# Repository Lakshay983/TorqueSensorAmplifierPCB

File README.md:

# TorqueSensorAmplifierPCB
PCB that amplifies an input signal from a torque sensor to be fed into an ADC

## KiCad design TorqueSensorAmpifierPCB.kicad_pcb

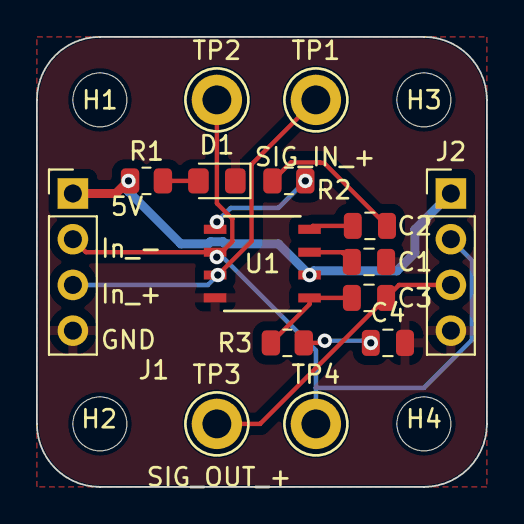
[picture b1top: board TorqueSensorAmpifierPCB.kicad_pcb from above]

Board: 2 copper layers, 25.0 x 25.0 mm, 19 parts (0 on the bottom side), 12 nets.

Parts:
C1: 1uF; C_0805_2012Metric
C2: 10uF; C_0805_2012Metric
C3: 250uF; C_0805_2012Metric
C4: .05uF; C_0805_2012Metric
D1: Green; LED_0805_2012Metric_Pad1.15x1.40mm_HandSolder
H1, H2, H3, H4: MountingHole; MountingHole_3mm
J1, J2: Conn_01x04_Socket; PinHeader_1x04_P2.54mm_Vertical
R1: 5k; R_0805_2012Metric
R2: 1.2k; R_0805_2012Metric
R3: 10; R_0805_2012Metric
TP1, TP2, TP3, TP4: TestPoint; TestPoint_Keystone_5005-5009_Compact
U1: LM386; M08A_TEX-L

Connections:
+5V: J1.1, J2.1, R1.1, U1.6 (V+)
/SIG_IN_+: J1.3, TP1.1, U1.3 (+)
/SIG_OUT_+: C3.2, J2.3, TP3.1
GND: C1.2, C4.2, D1.1 (K), J1.4, J2.4, U1.4 (GND)
GNDS: J1.2, J2.2, TP2.1, TP4.1, U1.2 (-)
unnamed: C2.1, U1.8 (GAIN)
unnamed: C2.2, R2.2
unnamed: C3.1, R3.1, U1.5
unnamed: C4.1, R3.2
unnamed: D1.2 (A), R1.2
unnamed: R2.1, U1.1 (GAIN)
unnamed: C1.1, U1.7 (BYPASS)

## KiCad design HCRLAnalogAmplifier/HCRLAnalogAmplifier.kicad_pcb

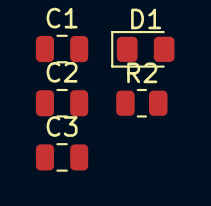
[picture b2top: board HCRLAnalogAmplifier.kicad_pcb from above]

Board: 2 copper layers, 5 parts (0 on the bottom side), 2 nets, no tracks yet.

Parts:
C1, C2, C3: C; C_0805_2012Metric
D1: Green; LED_0805_2012Metric_Pad1.15x1.40mm_HandSolder
R2: R; R_0805_2012Metric

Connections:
GND: C3.2, D1.1 (K)
unnamed: C1.2, R2.2

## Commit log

2023-11-15 started Torque Schematic
2023-11-15 Added torque schematic
2023-11-16 Added Gerbers
2023-11-16 Added BOMs
2023-11-22 Made it work for KiCAD 7
2023-11-22 build fix
2023-11-22 Fix .kibot.yaml path
2023-11-22 Add output directories
2023-11-22 Remove DRC and ERC
